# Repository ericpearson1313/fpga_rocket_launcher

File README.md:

### fpga_rocket_launcher

A long-time hobby of mine is model rocketry where I build and fly models rockets in a club setting.
A launch controller has a push button to electrically launch the models safely from a distance.
The controller feeds current from a battery, through a push button and lead wires to a resistive heater to initiate the launch.
For something so simple it causes consternation when the launch countdown reaches zero, button is pressed, and nothing, due to a fault of the controller!
Years of itteratively building launch controllers has not yet acheived personal perfection in launch controller design, but I'm having fun trying.

This repo contains my design files for a digital, capacitive discharch, launch controller. It was designed as a one-off fully instrumented 
launch controller based on a FPGA which enables built in oscilloscope-like capture and HDMI display. This provides aid in bring-up, observation of algorithm improvements and field analysis during fail-to-launch scenarios to understand how a launch fails (and adjust the design algorithms accordingly, and repeat). 

### Updates / Branches

Well this project has evolved alot. 

The launch controller, fully instrumented, gave me alot of observations of sucessful and failed operations. Burn-through makes this a unique control problem, and when obsereved closely is quite chaotic. Through itterative development and testing I updated the control algorithms and circuits. Alot more testing is needed, but the fpga core 'seems' solid, and my understanding of the initiation process has expanded greatly (and I can see alot more to understand).

Given the core fpga algorithms now for a simple handheld launch controller with rock solid operation.  

Integrating a chip deep within a simple device needs the insight of the development logic (ie hdmi) required tooling(fpgas) to breakout, connect, emulate, monitor, and simulating the system, and test the devices. This required a base architecture and plan to take advantage of the simple interconnect (a dozen I/O signals) available using the algorithm. Since this might be some effort,
planning went into the I/O so that it could address a number of device types in case I wanted to re-use it. The handheld controller was designed and is being trialled.

About this time the TinyTapeout.com course occured. This was an opportunity to move the core logic from Fpga to Asic. The same tooling could be used with an Asic too. 

An ASIC was deveoped integrating the launch control chip core. The system model was used as part of the verification test bench. With some time to spare a BIST (built in self test) was added which contained the system model and runs a 65ms truncated system simulation to self validate the hardware. [3D Chip viewer of the actual chip - way cool!](https://gds-viewer.tinytapeout.com/?model=https://ericpearson1313.github.io/tt_eric_launch/tinytapeout.oas&pdk=sky130A)

A quick outline of the different branches that have evolved. The readme docs on the branches are non existant so far.

- main : the fpga launch controller release (V6 = 7298ded) is in regular use.
- lcc_1K : isolated the MVP core and implemented it on a tiny 1k FPGA
- lcc_emu : is the full lauch controller ported to the lcc development board, and then re factoted to use the lcc_1k core and instrument it.
- lcc_mon : is a stand alone monitor that jsut looks at the signals of the LCC. Used to validate correct in system opeation
- lcc_syssim : is a system simulator (in progress) that connects to an LCC to test it.
- lcc_tt : is Tiny Tapeout chip in 130nm on a 0.2 x 0.16 mm die (1x2), it almost fit on a 1x1 tile, but not quite, so utilization is low.
- lccst_tt : is a Tiny Tapeout chip including a full self test (2x2) is 320x200um. The self test logic (a full system simulation) is almost 3x larger than the core, but gives me self test.

The original devlopement doc, where it all started, continues below

# Digital Model Rocket Launch Controller

A FPGA based model rocket digital launch controller.

No embedded CPU, this is Verilog RTL synthesized digital logic.

Showing a bench test using an Estes igniter. Observed low resistance (~ 1ohm) and takes 4 Joules at 4 amps for about 300msec.

[Schematic](fpga_blaster_schem_v0_8.pdf)

### Digital constant current capacitive discharge launch controller.

## Core function

Powered by 4xAA Lithium batteries capable 1A of current. 
When armed, the controller charges a 200uF capactor bank to 320V with a flyback converter giving 10 Joules of stored energy. 
Upon launch, the capacitor is discharged through a 390uH inductor into the igniter.
The discharge is modulated by a FET with a PWM gate drive.
Discharge is digitally current controlled as a buck converter with a setpoint in the range of 2.0 to 6.0 amps.
The set current is maintained over the full capacitor discharge, or until the ignitor burns through and the circuit opens.

The digital control system uses a differential analog front end, used to isolate and instrument the capacitor and output IVs.
12-bit ADCs sample the four signals (cap/out,I/V) which are simultaneously sampled and digitized at 3 Mhz and fed into the digital system.

The PWM signal is generated by a control loop running at 48 Mhz (16x sample rate). 
The control loop models the inductor current based on the PWM signal, ADC capcitor and output voltages (slowly changing), sample rate coil inductance. 
The PWM is turned on when ADC output current falls below a setpoint.
The PWM is turned off when the output current model rises above a setpoint,  
The model used for turn-off to avoid overshoot due to timing accuracy and sample latency.
A stable current pulse is generated limited only by the dropping capacitor voltage with a ripple limited only by the minimum PWM pulse width.

## Extended Functions

Additional uses for FPGA logic and real time ADC data stream can be implemented. These range from simple to Max Headroom.

### Charged LED Hysteresis.

Using the ADC stream include the capacitor voltage, the charge-LED could be operated to reflect the capacitor voltage charge with some hysteresis.
The logic would turn on the charge-LED when the capacitor voltage sample is received and reached 300V, as we want a full charge for launch, 
but would only turn off the charge-LED when the capacitor voltage falls below 50V (<3% energy) as we'ed like to know when it is safe to handle.

```
// Arm is based on vcap with 300v on thresh and 50v off thresh
logic cap_charged;
always @( posedge clk ) begin
	if( reset ) begin
		cap_charged <= 0;
	end else begin
		cap_charged <= ( strobe_d && vcap > (( 300 * 10000 ) / 2005 ) ) ? 1'b1 :
		               ( strobe_d && vcap < (( 50  * 10000 ) / 2005 ) ) ? 1'b0 : cap_charged;
	end
end
```

### Fire Button Debounce and Feedback.

Some dedicated logic to handle the lauch button input is worth while.

To make low cost push button feel nice required: adding debounce logic, and provide audio feedback of its operation. 
To do this debounce counters are used to measure at least 5ms of time before sensing a 'press',
and then generating a fixed 10msec pulse output for logic triggering, and 10msec C5 beep for feedback. 
100ms of release time was required before dectecting another button press. 

Multiple experments and measurements were done to get a basic good enough 'feeling' for this button. The audio feedback worked pleasantly well.

This button also had a long press detect feature to trigger additional functionality. 
If held for 600msec a 2nd signal output would be asserted while held.

### Pulse Energy Accumulation

Ignition energy is a key parameter of igniters. Mensurements
are usefull to check this value.

The instantaneous power (Watts) of the capacitor and outputs can
each be calculated from the ADC samples as E = I * V.

The energy (Joules) over a time period can be accumulated by the sum
of the power measurement.

Using 44 bit sum of product of the unscaled I and V ADC values during ignition period gives allows a 10 Joule range with uJ resolution.
Using the unscaled ADC data elimiates numerical error accumulation. For display the nearest decimal point position was chosen from the 44 bit number
and fixed point hexadecimal coding used for display. 
```
// Acculuate both Cap and Output power products.
always @(posedge clk) begin
	strobe_d <= ad_strobe;
	// P = I * V
   pout[21:0] <= vout[10:0] * iout[10:0];
   pcap[21:0] <= vcap[10:0] * icap[10:0];
	if( strobe_d ) begin
		acc_flag_d <= acc_flag;
		// raw power loaded at flag rise, acculuated during flag, and held afterwards
		eout[43:0] <= ( acc_flag && !acc_flag_d ) ? { 22'b0, pout[21:0] } : ( acc_flag ) ? ({ 22'b0, pout[21:0] } + eout[43:0]) : eout[43:0];
		ecap[43:0] <= ( acc_flag && !acc_flag_d ) ? { 22'b0, pcap[21:0] } : ( acc_flag ) ? ({ 22'b0, pcap[21:0] } + ecap[43:0]) : ecap[43:0];
	end else begin
		acc_flag_d <= acc_flag_d;
		eout[43:0] <= eout[43:0];
		ecap[43:0] <= ecap[43:0];
	end
end
```

Measuring power of both the output and capactor gives insights into the device efficiency and 
some redundancy for measurement validation.

### Continuity Checking

Checking the continuity of an igniter is a resistance measurement to 
check for cases where the circuit is open or shorted.

After the system is armed and waiting for launch, once per second, a 1usec PWM pulse is generated.
Ohms law, R = E / I, is performed on the ADC samples to derive a resistance.

The resistance is averaged and shown to be repeatable over the range 0.4 to 30.0 ohms.

Thresholds are applied to the resistance to decide when the continuity LED is turned on (1.0 to 16 ohms),
and a beep code is generated (A mute dip switch stops the beep codes after the first)

```
1 beep - OK, 1.0 to 8 Ohms
2 beeps - HI, over 8 ohms, but not open
3 beeps - Open circuit,
4 beeps - SHORT circuit maybe, under 1.0 ohms
```
Note: the energy output for this short pulse is accumulated and displayed by the previous function
and usually under 0.25 mJoules which is not enough for ignition.

### HDMI VGA output

Normally on-board LEDs are usefull during development debug to present state to give some insight into
correct operation. Usually there are never enough LEDs as state can get quite involved. 

The next steps usually involve: oscilloscopes, logic analysers, computers and software, however ...

LEDs can be replaced with pixels on an HDMI display. FPGA logic to generate HDMI outputs at XVGA 800x480x60Hz resolution is accomplished
with a 32Mhz pixel clock, and DDR LVDS outputs clocked at 160Mhz giving 320mbit ea for Red, Green and Blue. Digtal counters are used
to generate the video syncronization and maintain the current X and Y locations on the screen.

Connecting an internal signal to a given pixel can be as simple as the logical AND of test signal and desired pixel location, 
with all pels being ORed together to make the video signal
```
assign pel1 = (xcount == 100) & (ycount == 300) & (test_signal1 == 1);
assign pel2 = (xcount == 100) & (ycount == 310) & (test_signal2 == 1);
assign video = pel1 | pel2
```
With some additional logic a font set can be derived giving live text display of binary or hex measurements and dynamic text overlays like:
```
	string_overlay #(.LEN( 9)) _id4 (.clk(hdmi_clk), .reset(reset), .char_x(char_x), .char_y(char_y),
	.ascii_char(ascii_char), .x('h02),.y('h03), .out(id_str[4]), 
	.str(	( zoom == 0 ) ? " 21us/div" :
			( zoom == 1 ) ? " 43us/div" :
			( zoom == 2 ) ? " 85us/div" :
			( zoom == 3 ) ? "170us/div" :
			( zoom == 4 ) ? "340us/div" :
			( zoom == 5 ) ? "680us/div" :
			( zoom == 6 ) ? "1.4ms/div" :
			( zoom == 7 ) ? "2.7ms/div" :
			( zoom == 8 ) ? "5.5ms/div" :
			( zoom == 9 ) ? " 11ms/div" :
			( zoom == 10) ? " 22ms/div" :
			( zoom == 11) ? " 44ms/div" :
			/*zoom == 12)*/ " 87ms/div" ) );
```
Using this method logic was built to allow the display of live values: igniter resistance (ohms), capacitor and output energy (Joules), average ADC binary values, error statuses for ADC channels and PSRAM. Fixed point hex values are used for sake of logic simplicty. Noting that 5 hex digits ~ 1 million is helpful.

### Scrolling Oscilloscope

The 3Mhz ADC samples can have min and max values calculated over longer intervals (1/60s) can be stored
into a 500 sample buffer and plotted and overlayed onto the display giving insight into the coarse
operation of the capacitor charge and discharge without missing a single transient during PWM operation
and allowing sufficient time to visually observer operation. 

This display scrolling is halted 4 seconds after launch to show complete capacitor discharge.

### 32 MBytes Trace Buffer

A PSRAM, or pseudo SRAM, is alow cost ($10), high density (32 Mbytres), high speed (400MBs) sram-like memory, that can connects using only 11 signals. 
It has built in refresh logic, and uses a SPI8 interface for burst access.
A simple controller with an AXI4 interface was developed to configure and 
access the device with 16 byte burst writes, and both 8-byte or 64-byte burst reads.

These PSRAM are only available in ball grid array (BGA) footprints. This was my first home assembled PCB with a BGA. YouTube helped alot for that.

The ADC sampels are stored to a 32 Mbyte circular trace buffer. With 3 Mhz sampling and 64 bits per sample we get 1.3 seconds of storage, which is 
sufficient to capture the full launch operation. 64 bits allows capturing of the 4x 12-bit adc samples, as well as the sampled model (estimated current)
and sampled PWM, and push-button signals as well as an burn-through detect signal.

The buffer is written continuously and only is stopped after launch finished, captureing the full detail from slightly before the launch button is pressed.

### Trace Buffer Display

The 800 samples of data is read from the trace buffer during video blanking and used to plot the sample data multiple scales and colors.
The starting address and stride allows examing the data from very coarse to finest full 3 Mhz detail. 

After launch the fire button is used to step through zoom ranges to see what occured during launch.

### Blipvert

A blipvert is a very brief television advertisement, lasting one second. The term and concept were used in the 1985 film Max Headroom: 20 Minutes into the Future.

HDMI provides a fast and standards compliant way to upload the 32 Mbyte trace buffer to a computer.
The memory is dumped to the RGB video HDMI output, with each visible display line having an memory address
followed by 1 kbyte of data all encoded into the RGB pixels.

This looks like a burst of messy noise, which matched my memory of the blipvert from the film. 

The bipvert is activated by holding down the fire button for at least 1 second and continously dumps the buffer.

Using an HDMI capture card and capturing a second of the video noise gives the entire memory contents,
which can be recovered with a script from the captured video.

#### Blipvert Update #1

The 1st issue is that HDMI capture devices for RGB are costly ($300-$400), but are available
for $20 if a YUV color space is used. That is because the base USB protocol inlcudes support and drivers
for cameras and the cheap HDMI-USB capturee devices only support YUV2 protocol.

So what I planned and did was to switch over to YUV2 during blipvert operation. 
This meant inserting HDMI InfoFrame packets during video blanking, so each viedo frame could be identified
as either RGB24 or YUV2 coded. This swithcing worked.

This raised the 2nd issue was that my awesome and pricy sunlight viewable LCD display only supported the DVI subset of HDMI,
and the presence of InfoFrame packets caused issues. And the HDMI capture device required that the InfoFrames
must always be transmitted (or never transmitted).

The solution was to take advantage of the 2 HDMI ports and simultaneously transmit DVI for the LCD display and HDMI to external devices,
such as the Cheap USB capture device or an LCD display.

### Text Overlay

In addition to the dynamic logic derived text it is useful to have some fixed text overlay.

ROM equivalents for a 5x7 font table and a 16 color text overlay efficiently utilize the FPGA built in SRAMS. 
Unfortuately with this lowest cost (SC) version of the fpga, ROM initialization of the SRAMs is not available,
and the updated device costs 50% more. So logic was added to read the onboard flash and load it into the rom's (SRAMS). 

This text allowed my to display some basic static information without worrying about incremental gate cost if I modified the text.

### Git Commit ID

It is always helpful to be able to trace a running system back to its git commit. 

Some bash and awk scripting was used extract, format, and insert the 7 hex digit git commmit id into the text overlay 
(lower right corner) before the FPGA was compiled. Very handy

## FPGA Selection

The MAX-10 FPGAs from Intel/ALtera were selected as a) free tools were available and b) low cost devices and c) the instant-on (10mSec) boot time.
The 144 pin quad flat pack was chosen as it is hand solderable and probe-able. Devices from 2K to 25K logic cells are avaialable in pin compatible packages.
The free tools support System Verilog design input, and provide support integrating device specific features including differential and DDR IO and PLLs for clock generation. 

The design choice was the Intel Altera 10M04SCE144C8G, breaking down the part number:

```
10M - this family has free software tools.
04 - This was a $20 low cost device, has 4K Logic Elements (LEs) ).
SC - compact(cheap) device, no analog input, limited flash, no rom
E144 - Hand solderable quad flat pack
C - cheap consumer temps only
8G - cheap, slowest speedgrade
```

This 10M04 device also support pin compatibility over a 2 to 25K LE. 

The 10M04 is also a 'limited' device, in that
it is actually an 8K LE device and limited by software to only allow 4K usage. This allow the vendors to sell
their "Floor sweepings", and provides 1/2 cost devices to us. The neat part is that 100% utilization of the 4K LEs is 
then possible as which LEs are used remains flexible, and the interconnect is sized for higher densities, so it can
be fully packed to 99% utilization.

## Free Development Tools 

FPGA Dev Tools : Intel Altera Quartus Prime Lite v23.1

Schematic/PCB  : KiCad 7.0

## Capacitor discharge Pros and Cons

After this experience is a good time to reflect on the trade offs in
capactor discharge launch controllers vs a standard launch controller based with push button.

```
Pros:
+ Current Pulse delivers same power with any cabling
+ safety, can be part of an intrisically safe system
+ Resistance Measurement with 0.1 ohm precision
+ Energy Measurement with 1 uJ precision 
+ Repeatability with constant current with minimal ripple
+ Failure Analysys Data
+ Portable, with small battery
+ Battery Life is extended 
+ Reliability, Feedback gives confidence  

Cons:
- Button - it still needs a push button, and can be replaced by a push button.
- Expensive
- Estes - does not work well with estes igniters
- Complex system
- High Voltage and Arcing
- Majority of limited capacitor energy can be dissipated in launch leads and connections.
```

### A ForgeFPGA-1K implementation

Update: A ForgeFPGA implementation. 

I came across ForgeFPGAs which are 3x3mmm low power low cost ($0.50) FPGA chips containing a respectable 1120 logic cells. 
The 24 pins package had the IO needed and the logic cells seemed appropriate for a the launch controllers core functions.
The free tools for synthesis and place-route worked with my verilog code with minor tweaking.
With functional simplification (eg: no hdmi video, no dividers) the tools fit the core launch controller logic gates into 
the ForgeFPGA-1K and generated power and timing reports. 
I then verified the forgefpga verilog by embedding it into my altera max10 fpga launch controller allowing me to view the instrumented interface 
 between the co-synthesized core ForgeFPGA and the real hardware (very nice!).
I plan to use this launch control fpga for an minimalist handheld digital launch controller PCB. It would have connectors for mounting the ForgeFPGA Eval board for development, and would otherwise re-use the ADC and power circuitry interface as needed from the previous controller.

With the size of the FPGA now reduced to basically nothing, a compact size could be looked at. I stopped and considered the shapes limited by the large components: 4xAA, 2x Caps, 1x Coil, and along with output jacks. 3D printing each allowed some ergonomic testing and locating the 2 pairs of buttons and Leds.

A starting layout of the PCB using the landscape packing was chosen from among the models.
The landscape form factor nicely extends to put a connector for the ForgeFPGA evaluation board to be plugged into. That part of the PCB is intended to be cut away (but could be integrated into a taller handheld unit). Mouting land for a spare FPGA is nice. The isolation of high voltage areas is considered from the beginning.  The isolation barrier and components crossing it are clear and visible.
The layout packed the high power connections to the top center of the PCB.

Prior to fully detailing the PCB outline and button/led positions and clearnaces are needed.
I wanted to integrate the leds and buttons into the enclosure. Light pipes for the leds, and frogs
for the buttons. (frog aka pushbutton-with-integrated-spring-for-tactile-switch).
A basic 3d printed model of the enclosure was printed to see how it feels and test the frogs.
I definitely want it thinner and rounded/bevelled. The influence of this model will be far reaching in
the final design. 

Next steps for the minimalist fpga launch controller will be parts ordering, pcb tapeout, and initial 3d enclosure and development stands ...

Its a good point to pause and consider things. So I'm going to loop back and re-examine everything before committing to the next design...

# A Chip ...

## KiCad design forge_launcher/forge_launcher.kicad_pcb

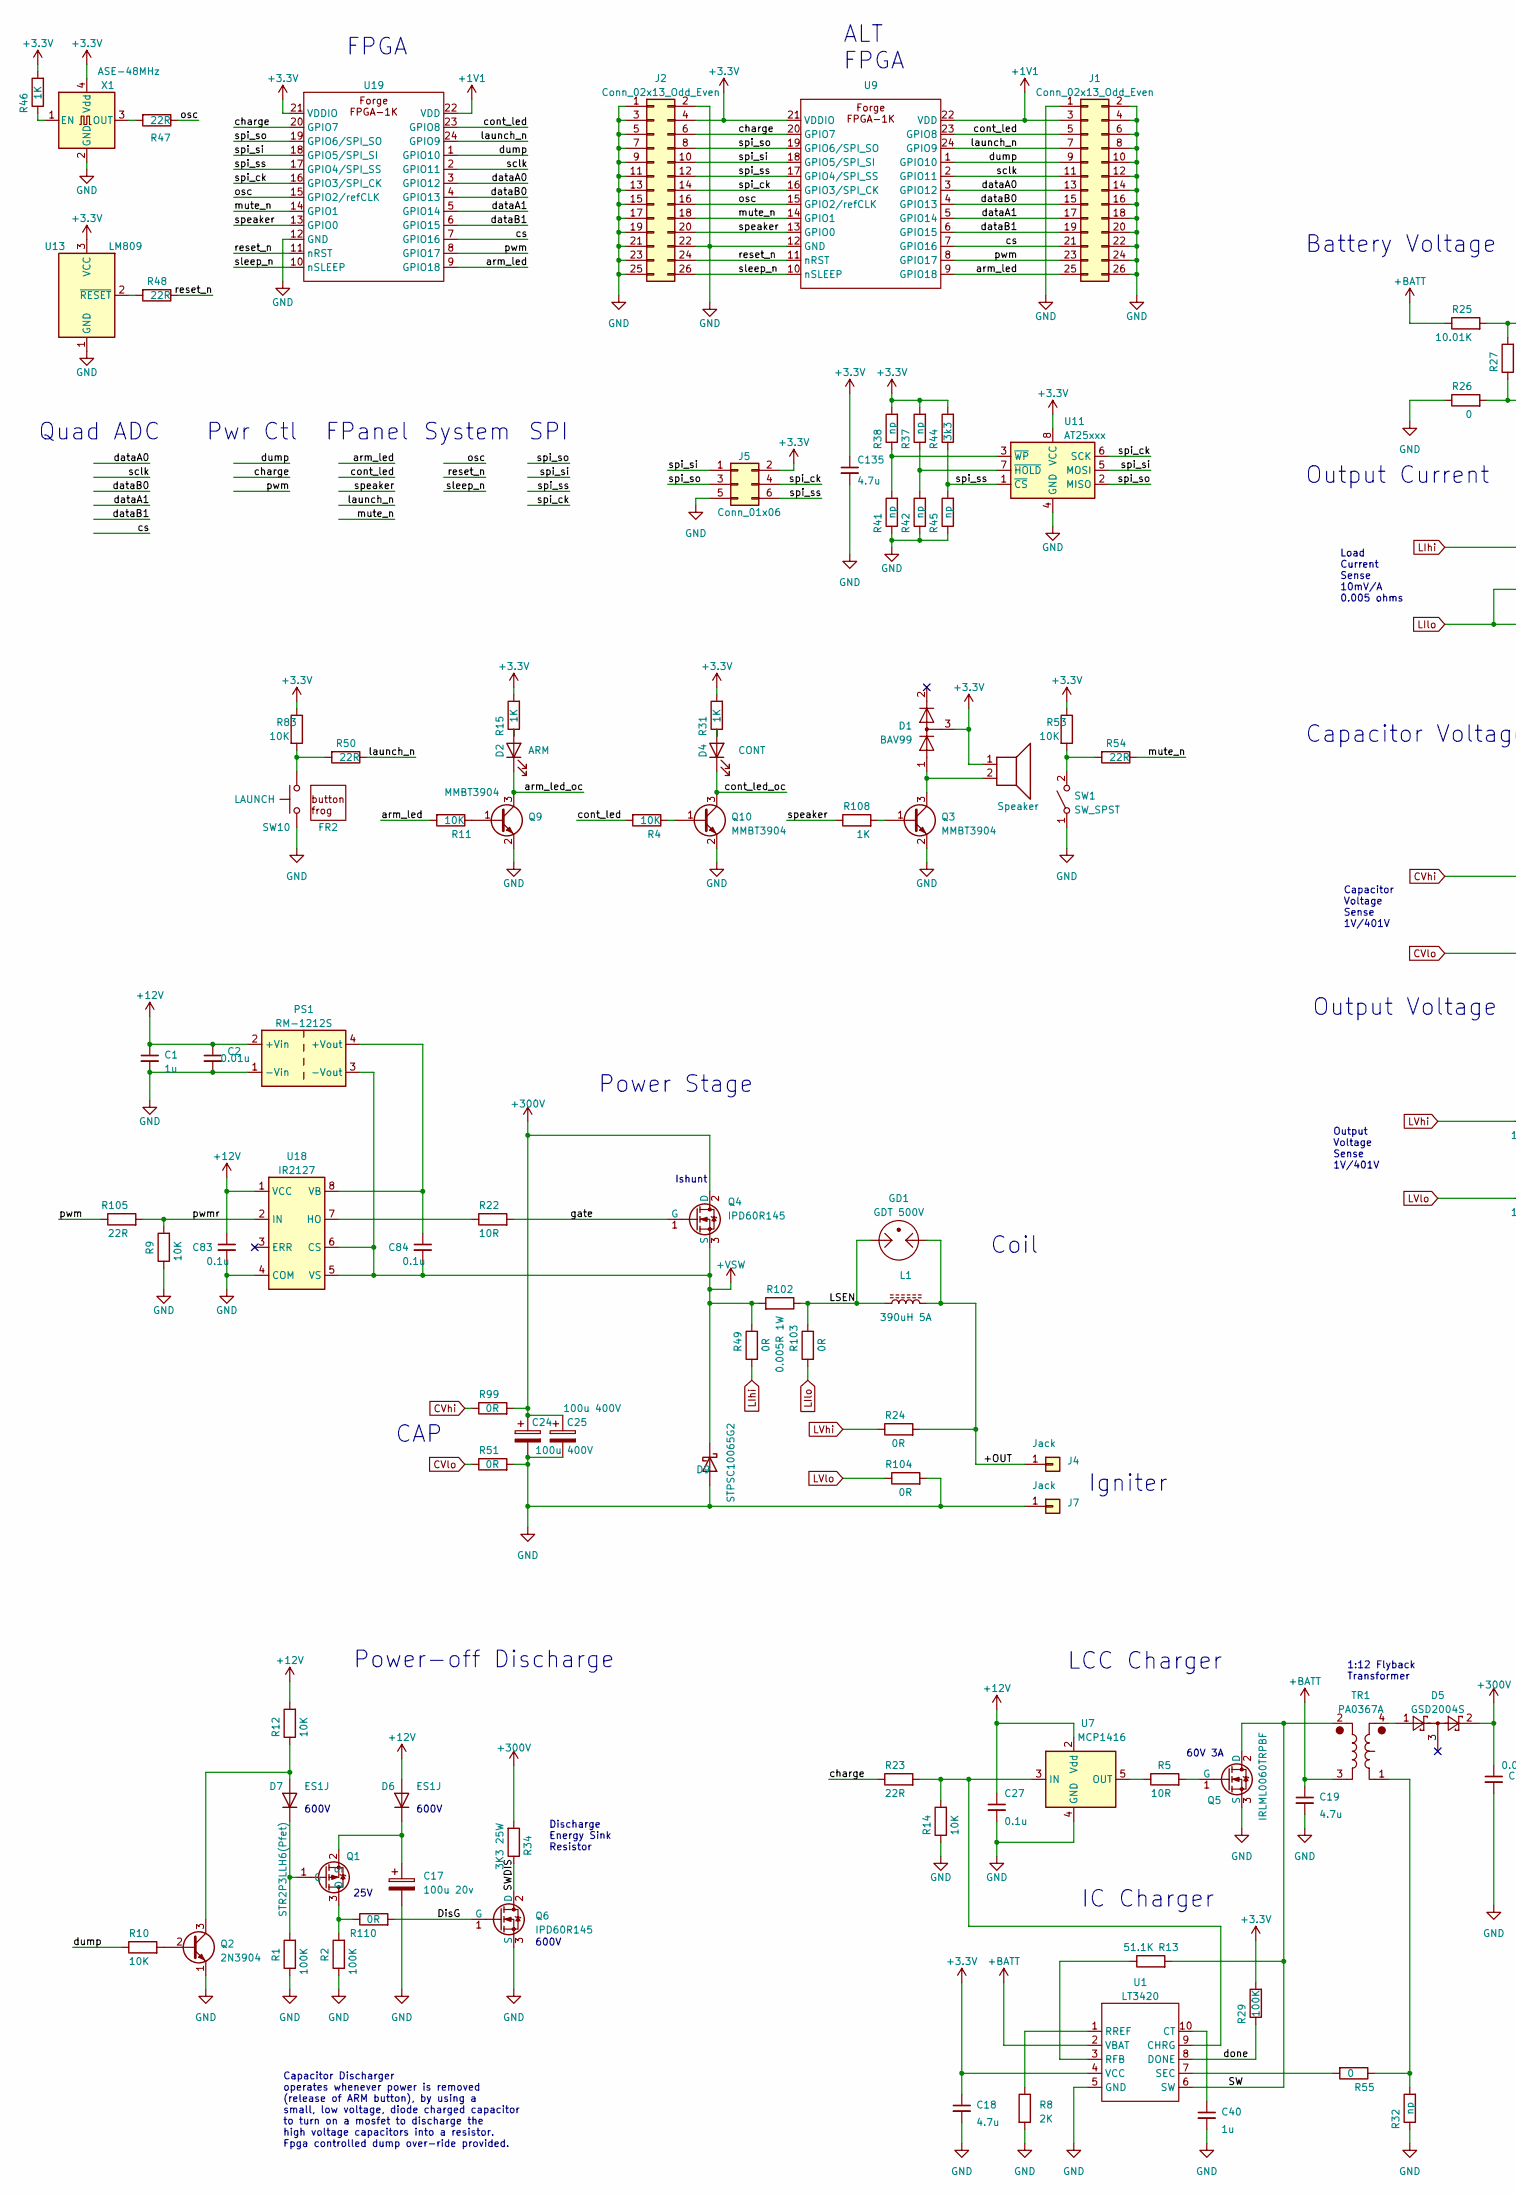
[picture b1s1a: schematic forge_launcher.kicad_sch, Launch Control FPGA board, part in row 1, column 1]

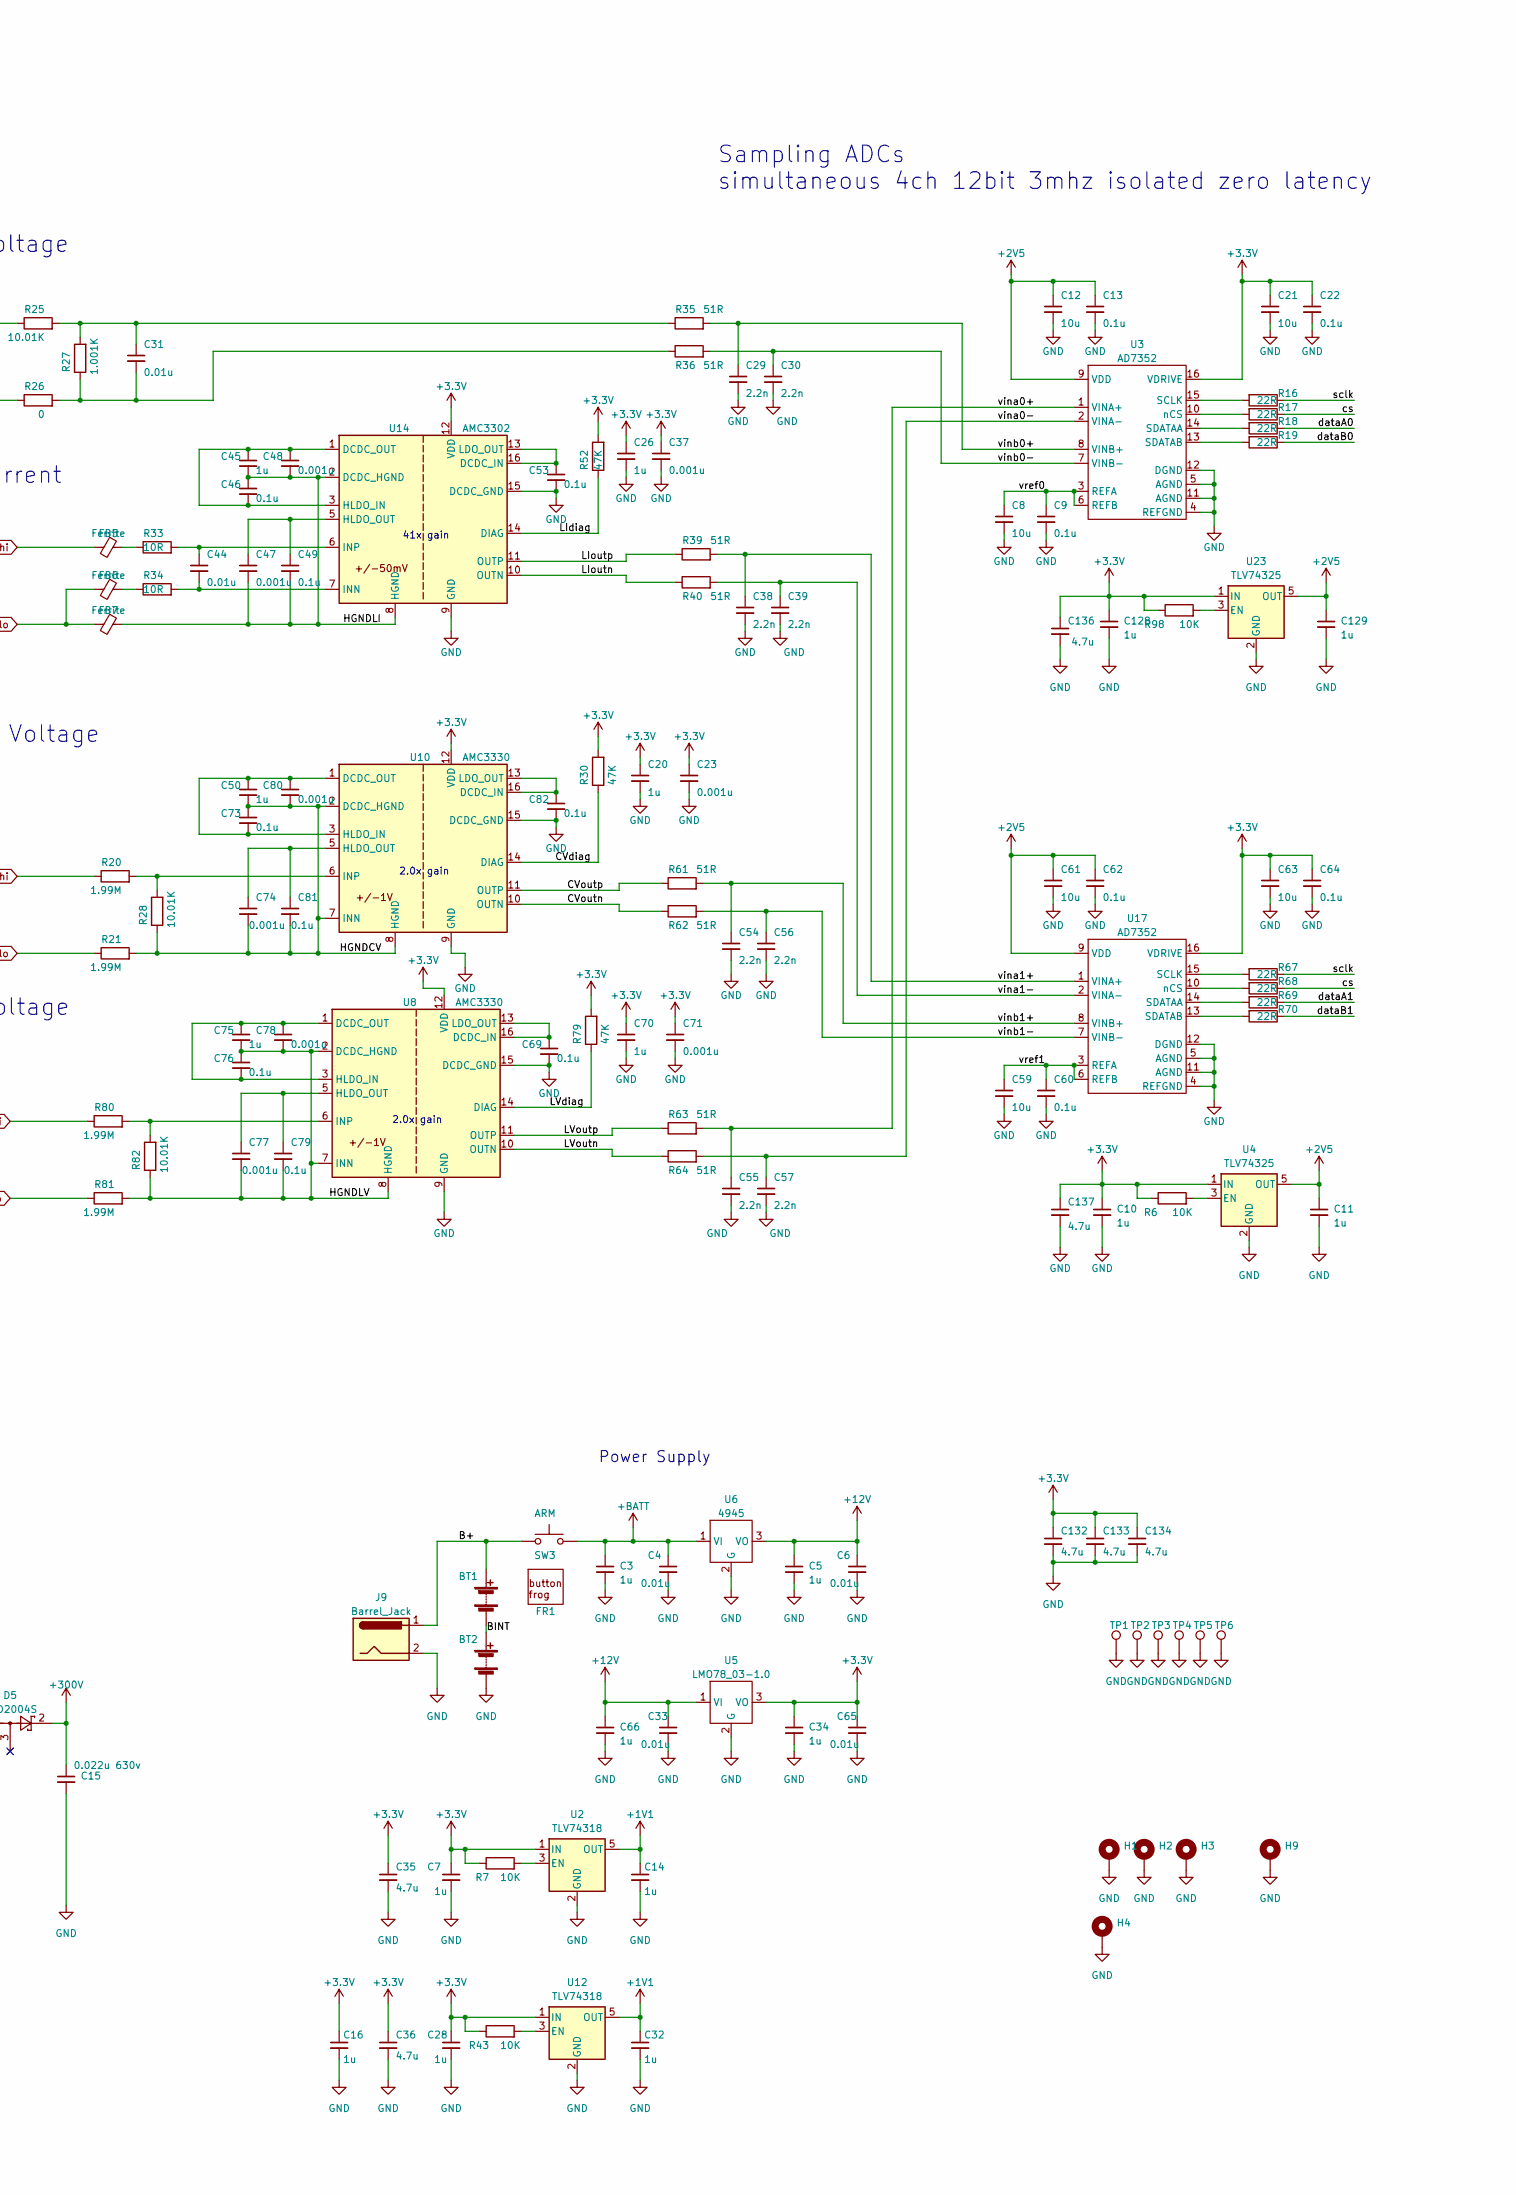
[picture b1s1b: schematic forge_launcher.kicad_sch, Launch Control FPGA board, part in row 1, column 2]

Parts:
BT1, BT2: BatteryHolder_Keystone_2462_2xAA
C1, C3, C5, C7, C10, C11, C14, C16, C20, C26, C28, C32, C34, C40, C45, C50, C66, C70, C75, C128, C129: 1u; C_0603_1608Metric
C2, C4, C6, C31, C33, C44, C65: 0.01u; C_0603_1608Metric
C8, C12, C21, C59, C61, C63: 10u; C_1206_3216Metric
C9, C13, C22, C27, C46, C49, C53, C60, C62, C64, C69, C73, C76, C79, C81, C82, C83, C84: 0.1u; C_0603_1608Metric
C15: 0.022u 630v; C_1206_3216Metric
C17: 100u 20v; C_Radial_D5.0mm_H7.0mm_P2.00mm
C18, C19, C35, C36, C132, C133, C134, C135, C136, C137: 4.7u; C_1206_3216Metric
C23, C37, C47, C48, C71, C74, C77, C78, C80: 0.001u; C_0603_1608Metric
C24, C25: 100u 400V; CP_Radial_D16.0mm_P7.50mm
C29, C30, C38, C39, C54, C55, C56, C57: 2.2n; C_0603_1608Metric
D1: BAV99; SOT-23
D2: ARM; LED_0603_1608Metric
D4: CONT; LED_0603_1608Metric
D5: GSD2004S; SOT-23; JLC C85606
D6, D7: ES1J; D_SMA; JLC C99410
D9: ‎STPSC10065G2; TO-263-2_TabPin1; JLC C602663
FB5, FB6, FB7: Ferrite; L_0603_1608Metric
FR1, FR2: button_frog
GD1: GDT 500V; C_1812_4532Metric_Pad1.57x3.40mm_HandSolder
H1, H2, H3, H4, H9: MountingHole_3mm_Pad
J1, J2: Conn_02x13_Odd_Even
J4, J7: Jack; CalTest_CT3151
J5: Conn_01x06; PinHeader_2x03_P2.54mm_Vertical
J9: Barrel_Jack; BarrelJack_CUI_PJ-063AH_Horizontal
L1: 390uH 5A; L_Toroid_Vertical_L35.6mm_W17.8mm_P12.70mm_Pulse_E
LS1: Speaker; PUIAudio_SMT_0825_S_4_R
PS1: RM-1212S; Converter_DCDC_Murata_MEE1SxxxxSC_THT
Q1: STR2P3LLH6(Pfet); SOT-23
Q2: 2N3904; SOT-23
Q3, Q9, Q10: MMBT3904; SOT-23
Q4, Q6: IPD60R145; TO-252-2; JLC C3277918
Q5: IRLML0060TRPBF; SOT-23; JLC C3277918
R1, R2, R29: 100K; R_0603_1608Metric; JLC C319967
R4, R11: 10K; R_0603_1608Metric; JLC C319967
R5, R22, R33, R34: 10R; R_0603_1608Metric; JLC C778416
R6, R7, R43, R98: 10K; R_0603_1608Metric; JLC C778416
R8: 2K; R_0603_1608Metric; JLC C319700
R9, R12, R14, R53, R83: 10K; R_0603_1608Metric; JLC C491211
R10: 10K; R_0603_1608Metric
R13: 51.1K; R_0603_1608Metric; JLC C234563
R15, R31, R46, R108: 1K; R_0603_1608Metric; JLC C319967
R16, R17, R18, R19, R47, R48, R50, R54, R67, R68, R69, R70: 22R; R_0603_1608Metric; JLC C319967
R20, R21, R80, R81: 1.99M; R_0603_1608Metric; JLC C778416
R23, R105: 22R; R_0603_1608Metric; JLC C778416
R24, R49, R51, R99, R103, R104: 0R; R_0603_1608Metric; JLC C778416
R25, R28, R82: 10.01K; R_0603_1608Metric; JLC C778416
R26: 0; R_0603_1608Metric; JLC C778416
R27: 1.001K; R_0603_1608Metric; JLC C778416
R30, R52, R79: 47K; R_0603_1608Metric; JLC C778416
R32, R37, R38, R41, R42, R45: np; R_0603_1608Metric; JLC C319967
R35, R36, R39, R40, R61, R62, R63, R64: 51R; R_0603_1608Metric; JLC C778416
R44: 3k3; R_0603_1608Metric; JLC C319967
R55: 0; R_0603_1608Metric; JLC C319967
R102: 0.005R 1W; R_2818 current sense
R110: 0R; R_0603_1608Metric; JLC C319967
SW1: SW_SPST; SW_E-Switch_EG1224_SPDT_Angled
SW3: ARM; SW_SPST_HP03
SW10: LAUNCH; SW_SPST_HP03
TP1, TP2, TP3, TP4, TP5, TP6: TestPoint_Keystone_5000-5004_Miniature
TR1: PA0367A; PA0637A Pulse Coil 3D; JLC C5382098
U1: LT3420; MSOP-10_3x3mm_P0.5mm; JLC C670531
U2, U12: TLV74318; SOT-23-5
U3, U17: AD7352; TSSOP-16_4.4x5mm_P0.65mm
U4, U23: TLV74325; SOT-23-5
U5: LMO78_03-1.0; Converter_DCDC_Murata_OKI-78SR_Horizontal
U6: 4945; Converter_DCDC_Murata_OKI-78SR_Horizontal
U7: MCP1416; SOT-23-5
U8, U10: AMC3330; SOIC-16W_7.5x10.3mm_P1.27mm
U9, U19: QFN-24-3x3mm
U11: AT25xxx; SOIC-8_3.9x4.9mm_P1.27mm
U13: LM809; SOT-23
U14: AMC3302; SOIC-16W_7.5x10.3mm_P1.27mm
U18: IR2127; SOIC-8_3.9x4.9mm_P1.27mm; JLC C356723
X1: ASE-48MHz; Oscillator_SMD_Abracon_ASV-4Pin_7.0x5.1mm_HandSoldering

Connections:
+1V1: C14.1, C32.1, J1.3, U2.5 (OUT), U9.22 (VDD), U12.5 (OUT), U19.22 (VDD)
+2V5: C11.1, C12.1, C13.1, C61.1, C62.1, C129.1, U3.9 (VDD), U4.5 (OUT), U17.9 (VDD), U23.5 (OUT)
+3.3V: C7.1, C10.1, C16.1, C18.1, C20.1, C21.1, C22.1, C23.1, C26.1, C28.1, C34.1, C35.1, C36.1, C37.1, C63.1, C64.1, C65.1, C70.1, C71.1, C128.1, C132.1, C133.1, C134.1, C135.1, C136.1, C137.1, D1.3 (K), J2.4, J5.2, LS1.1, R6.1, R7.1, R15.2, R29.2, R30.2, R31.2, R37.2, R38.2, R43.1, R44.2, R46.2, R52.2, R53.1, R79.2, R83.1, R98.1, U1.4 (VCC), U2.1 (IN), U3.16 (VDRIVE), U4.1 (IN), U5.3 (VO), U8.12 (VDD), U9.21 (VDDIO), U10.12 (VDD), U11.8 (VCC), U12.1 (IN), U13.3 (VCC), U14.12 (VDD), U17.16 (VDRIVE), U19.21 (VDDIO), U23.1 (IN), X1.4 (Vdd)
+12V: C1.1, C2.1, C5.1, C6.1, C27.1, C33.1, C66.1, C83.1, D6.2 (A), PS1.2 (+Vin), R12.2, U5.1 (VI), U6.3 (VO), U7.2 (Vdd), U18.1 (VCC)
+BATT: C3.1, C4.1, C19.1, R25.1, SW3.2, TR1.3, U1.2 (VBAT), U6.1 (VI)
+VSW: C84.2, D9.1 (K), PS1.3 (-Vout), Q4.3 (S), R49.1, R102.2, U18.5 (VS), U18.6 (CS)
/+OUT: GD1.1, J4.1, L1.2, R24.2
/B+: BT1.1 (+), J9.1, SW3.1
/BINT: BT1.2 (-), BT2.1 (+)
/CVdiag: R30.1, U10.14 (DIAG)
/CVoutn: R62.1, U10.10 (OUTN)
/CVoutp: R61.1, U10.11 (OUTP)
/DisG: Q6.1 (G), R110.2
/HGNDCV: C50.2, C73.1, C74.2, C80.2, C81.2, R21.2, R28.1, U10.2 (DCDC_HGND), U10.7 (INN), U10.8 (HGND)
/HGNDLI: C45.2, C46.1, C47.2, C48.2, C49.2, FB7.1, U14.2 (DCDC_HGND), U14.8 (HGND)
/HGNDLV: C75.2, C76.1, C77.2, C78.2, C79.2, R81.2, R82.1, U8.2 (DCDC_HGND), U8.7 (INN), U8.8 (HGND)
/LIdiag: R52.1, U14.14 (DIAG)
/LIoutn: R40.1, U14.10 (OUTN)
/LIoutp: R39.1, U14.11 (OUTP)
/LSEN: GD1.3, L1.1, R102.1, R103.1
/LVdiag: R79.1, U8.14 (DIAG)
/LVoutn: R64.1, U8.10 (OUTN)
/LVoutp: R63.1, U8.11 (OUTP)
/SW: Q5.2 (D), R13.2, TR1.2, U1.6 (SW)
/arm_led: J1.25, R11.2, U9.9 (GPIO18), U19.9 (GPIO18)
/arm_led_oc: D2.1 (K), Q9.3 (C)
/charge: J2.6, R23.1, U9.20 (GPIO7), U19.20 (GPIO7)
/cont_led: J1.5, R4.2, U9.23 (GPIO8), U19.23 (GPIO8)
/cont_led_oc: D4.1 (K), Q10.3 (C)
/cs: J1.21, R17.1, R68.1, U9.7 (GPIO16), U19.7 (GPIO16)
/dataA0: J1.13, R18.1, U9.3 (GPIO12), U19.3 (GPIO12)
/dataA1: J1.17, R69.1, U9.5 (GPIO14), U19.5 (GPIO14)
/dataB0: J1.15, R19.1, U9.4 (GPIO13), U19.4 (GPIO13)
/dataB1: J1.19, R70.1, U9.6 (GPIO15), U19.6 (GPIO15)
/done: R29.1, U1.8 (DONE)
/dump: J1.9, R10.1, U9.1 (GPIO10), U19.1 (GPIO10)
/gate: Q4.1 (G), R22.2
/launch_n: J1.7, R50.1, U9.24 (GPIO9), U19.24 (GPIO9)
/mute_n: J2.18, R54.1, U9.14 (GPIO1), U19.14 (GPIO1)
/osc: J2.16, R47.1, U9.15 (GPIO2/refCLK), U19.15 (GPIO2/refCLK)
/pwm: J1.23, R105.1, U9.8 (GPIO17), U19.8 (GPIO17)
/pwmr: R9.2, R105.2, U18.2 (IN)
/reset_n: J2.24, R48.1, U9.11 (nRST), U19.11 (nRST)
/sclk: J1.11, R16.1, R67.1, U9.2 (GPIO11), U19.2 (GPIO11)
/sleep_n: J2.26, U9.10 (nSLEEP), U19.10 (nSLEEP)
/speaker: J2.20, R108.1, U9.13 (GPIO0), U19.13 (GPIO0)
/spi_ck: J2.14, J5.4, U9.16 (GPIO3/SPI_CK), U11.6 (SCK), U19.16 (GPIO3/SPI_CK)
/spi_si: J2.10, J5.1, U9.18 (GPIO5/SPI_SI), U11.5 (MOSI), U19.18 (GPIO5/SPI_SI)
/spi_so: J2.8, J5.3, U9.19 (GPIO6/SPI_SO), U11.2 (MISO), U19.19 (GPIO6/SPI_SO)
/spi_ss: J2.12, J5.6, R44.1, R45.2, U9.17 (GPIO4/SPI_SS), U11.1 (~CS), U19.17 (GPIO4/SPI_SS)
/vina0+: C55.1, R63.2, U3.1 (VINA+)
/vina0-: C57.1, R64.2, U3.2 (VINA-)
/vina1+: C38.1, R39.2, U17.1 (VINA+)
/vina1-: C39.1, R40.2, U17.2 (VINA-)
/vinb0+: C29.1, R35.2, U3.8 (VINB+)
/vinb0-: C30.1, R36.2, U3.7 (VINB-)
/vinb1+: C54.1, R61.2, U17.8 (VINB+)
/vinb1-: C56.1, R62.2, U17.7 (VINB-)
/vref0: C8.1, C9.1, U3.3 (REFA), U3.6 (REFB)
/vref1: C59.1, C60.1, U17.3 (REFA), U17.6 (REFB)
CVhi: R20.1, R99.1
CVlo: R21.1, R51.1
GND: BT2.2 (-), C1.2, C2.2, C3.2, C4.2, C5.2, C6.2, C7.2, C8.2, C9.2, C10.2, C11.2, C12.2, C13.2, C14.2, C15.2, C16.2, C17.2, C18.2, C19.2, C20.2, C21.2, C22.2, C23.2, C24.2, C25.2, C26.2, C27.2, C28.2, C29.2, C30.2, C32.2, C33.2, C34.2, C35.2, C36.2, C37.2, C38.2, C39.2, C40.2, C53.2, C54.2, C55.2, C56.2, C57.2, C59.2, C60.2, C61.2, C62.2, C63.2, C64.2, C65.2, C66.2, C69.2, C70.2, C71.2, C82.2, C83.2, C128.2, C129.2, C132.2, C133.2, C134.2, C135.2, C136.2, C137.2, D9.2 (A), H1.1, H2.1, H3.1, H4.1, H9.1, J1.1, J1.2, J1.4, J1.6, J1.8, J1.10, J1.12, J1.14, J1.16, J1.18, J1.20, J1.22, J1.24, J1.26, J2.1, J2.2, J2.3, J2.5, J2.7, J2.9, J2.11, J2.13, J2.15, J2.17, J2.19, J2.21, J2.22, J2.23, J2.25, J5.5, J7.1, J9.2, PS1.1 (-Vin), Q2.1 (E), Q3.2 (E), Q5.3 (S), Q6.3 (S), Q9.2 (E), Q10.2 (E), R1.1, R2.1, R8.2, R9.1, R14.1, R26.1, R32.1, R41.1, R42.1, R45.1, R51.2, R104.2, SW1.1 (A), SW10.1, TP1.1, TP2.1, TP3.1, TP4.1, TP5.1, TP6.1, U1.5 (GND), U2.2 (GND), U3.4 (REFGND), U3.5 (AGND), U3.11 (AGND), U3.12 (DGND), U4.2 (GND), U5.2 (G), U6.2 (G), U7.4 (GND), U8.9 (GND), U8.15 (DCDC_GND), U9.12 (GND), U10.9 (GND), U10.15 (DCDC_GND), U11.4 (GND), U12.2 (GND), U13.1 (GND), U14.9 (GND), U14.15 (DCDC_GND), U17.4 (REFGND), U17.5 (AGND), U17.11 (AGND), U17.12 (DGND), U18.4 (COM), U19.12 (GND), U23.2 (GND), X1.2 (GND)
LIhi: FB5.2, R49.2
LIlo: FB6.2, FB7.2, R103.2
LVhi: R24.1, R80.1
LVlo: R81.1, R104.1
unnamed: C31.1, R25.2, R27.2, R35.1
unnamed: C31.2, R26.2, R27.1, R36.1
unnamed: D2.2 (A), R15.1
unnamed: D4.2 (A), R31.1
unnamed: D5.1, TR1.4
unnamed: C17.1, D6.1 (K), Q1.2 (S)
unnamed: D7.2 (A), Q2.3 (C), R12.1
unnamed: D7.1 (K), Q1.1 (G), R1.2
unnamed: FB5.1, R33.1
unnamed: C84.1, PS1.4 (+Vout), U18.8 (VB)
unnamed: Q1.3 (D), R2.2, R110.1
unnamed: Q2.2 (B), R10.2
unnamed: Q3.1 (B), R108.2
unnamed: D1.1 (K), LS1.2, Q3.3 (C)
unnamed: Q5.1 (G), R5.2
unnamed: Q9.1 (B), R11.1
unnamed: Q10.1 (B), R4.1
unnamed: R32.2, R55.1, TR1.1
unnamed: R50.2, R83.2, SW10.2
unnamed: R53.2, R54.2, SW1.2 (B)
unnamed: R14.2, R23.2, U1.9 (CHRG), U7.3 (IN)
unnamed: C40.1, U1.10 (CT)
unnamed: R13.1, U1.3 (RFB)
unnamed: R8.1, U1.1 (RREF)
unnamed: R55.2, U1.7 (SEC)
unnamed: R7.2, U2.3 (EN)
unnamed: R16.2, U3.15 (SCLK)
unnamed: R18.2, U3.14 (SDATAA)
unnamed: R19.2, U3.13 (SDATAB)
unnamed: R17.2, U3.10 (nCS)
unnamed: R6.2, U4.3 (EN)
unnamed: R5.1, U7.5 (OUT)
unnamed: C69.1, U8.13 (LDO_OUT), U8.16 (DCDC_IN)
unnamed: C75.1, C76.2, C78.1, U8.1 (DCDC_OUT), U8.3 (HLDO_IN)
unnamed: C77.1, C79.1, U8.5 (HLDO_OUT)
unnamed: R80.2, R82.2, U8.6 (INP)
unnamed: C82.1, U10.13 (LDO_OUT), U10.16 (DCDC_IN)
unnamed: C50.1, C73.2, C80.1, U10.1 (DCDC_OUT), U10.3 (HLDO_IN)
unnamed: C74.1, C81.1, U10.5 (HLDO_OUT)
unnamed: R20.2, R28.2, U10.6 (INP)
unnamed: R37.1, R42.2, U11.7 (~HOLD)
unnamed: R38.1, R41.2, U11.3 (~WP)
unnamed: R43.2, U12.3 (EN)
unnamed: R48.2, U13.2 (~RESET)
unnamed: C53.1, U14.13 (LDO_OUT), U14.16 (DCDC_IN)
unnamed: C45.1, C46.2, C48.1, U14.1 (DCDC_OUT), U14.3 (HLDO_IN)
unnamed: C47.1, C49.1, U14.5 (HLDO_OUT)
unnamed: C44.1, R33.2, U14.6 (INP)
unnamed: R67.2, U17.15 (SCLK)
unnamed: R69.2, U17.14 (SDATAA)
unnamed: R70.2, U17.13 (SDATAB)
unnamed: R68.2, U17.10 (nCS)
unnamed: R22.1, U18.7 (HO)
unnamed: R98.2, U23.3 (EN)
unnamed: R46.1, X1.1 (EN)
unnamed: R47.2, X1.3 (OUT)

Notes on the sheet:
600V
Power-off Discharge
Igniter
Quad ADC
Capacitor Voltage
41x gain
Coil
Capacitor Voltage Sense 1V/401V
Output Voltage
SPI
Ishunt
Output Voltage Sense 1V/401V
Sampling ADCs simultaneous 4ch 12bit 3mhz isolated zero latency
CAP
2.0x gain
FPGA
25V
IC Charger
System
Pwr Ctl
FPanel
ALT FPGA
Discharge Energy Sink Resistor
60V 3A
Power Supply
Power Stage
Output Current
Battery Voltage
Load Current Sense 10mV/A 0.005 ohms
Capacitor Discharger operates whenever power is removed (release of ARM button), by using a small, low voltage, diode charged capacitor to turn on a mosfet to discharge the high voltage capacitors into a resistor. Fpga controlled dump over-ride provided.
1:12 Flyback Transformer
LCC Charger

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
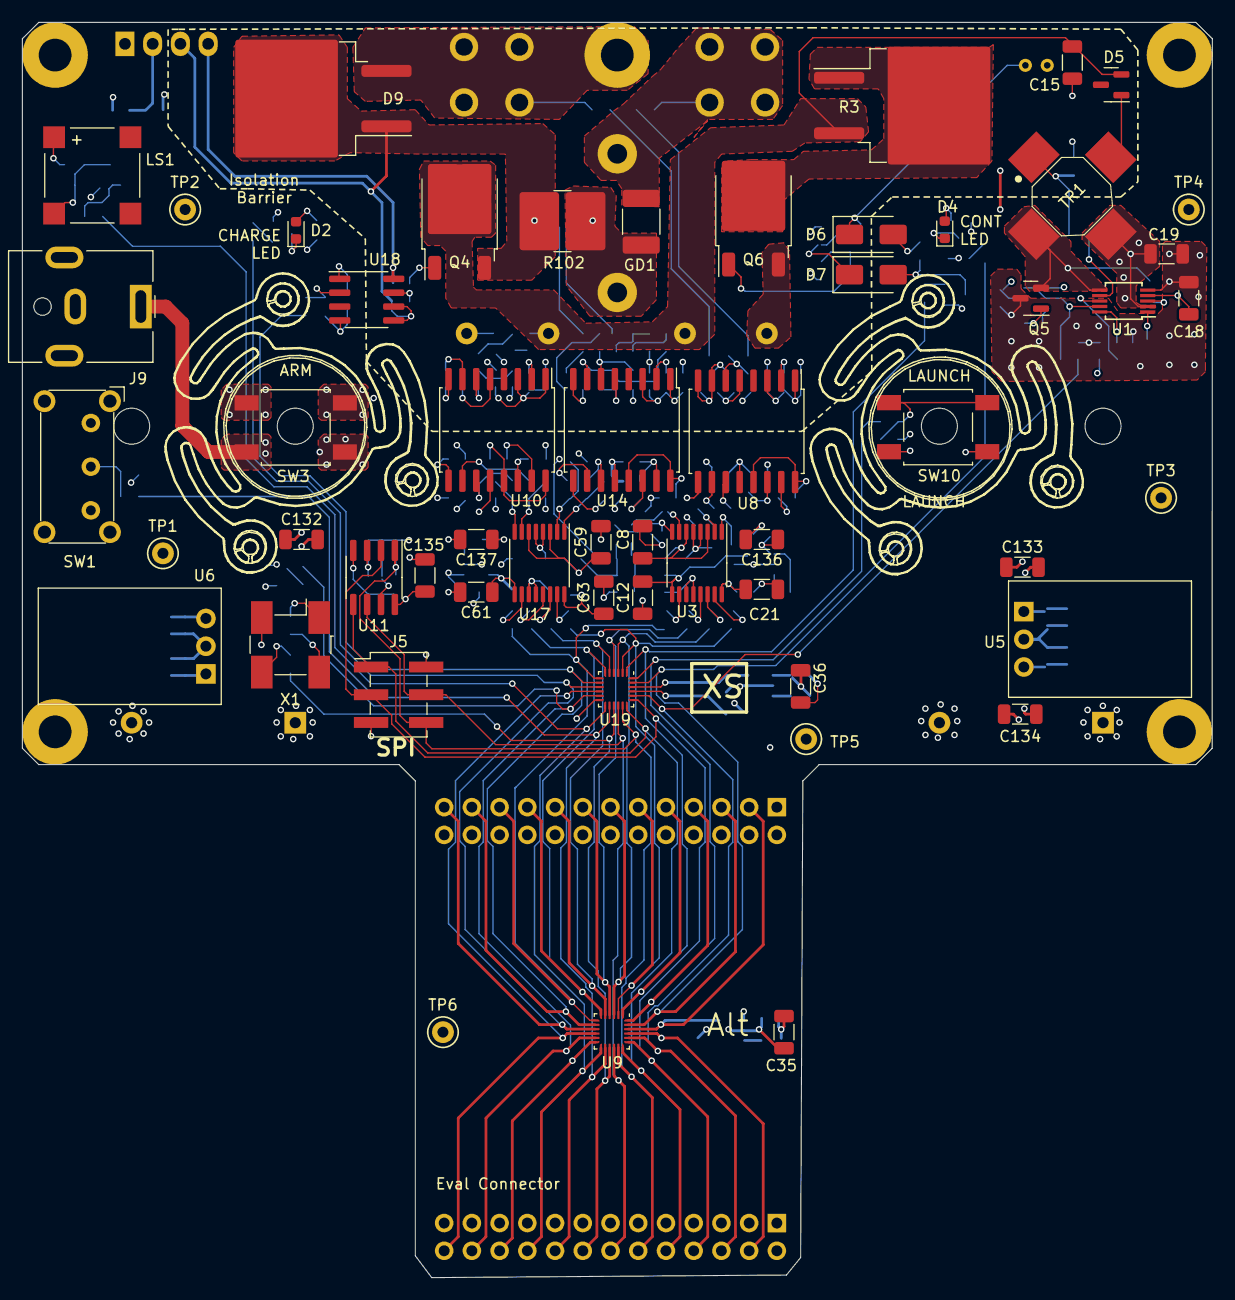
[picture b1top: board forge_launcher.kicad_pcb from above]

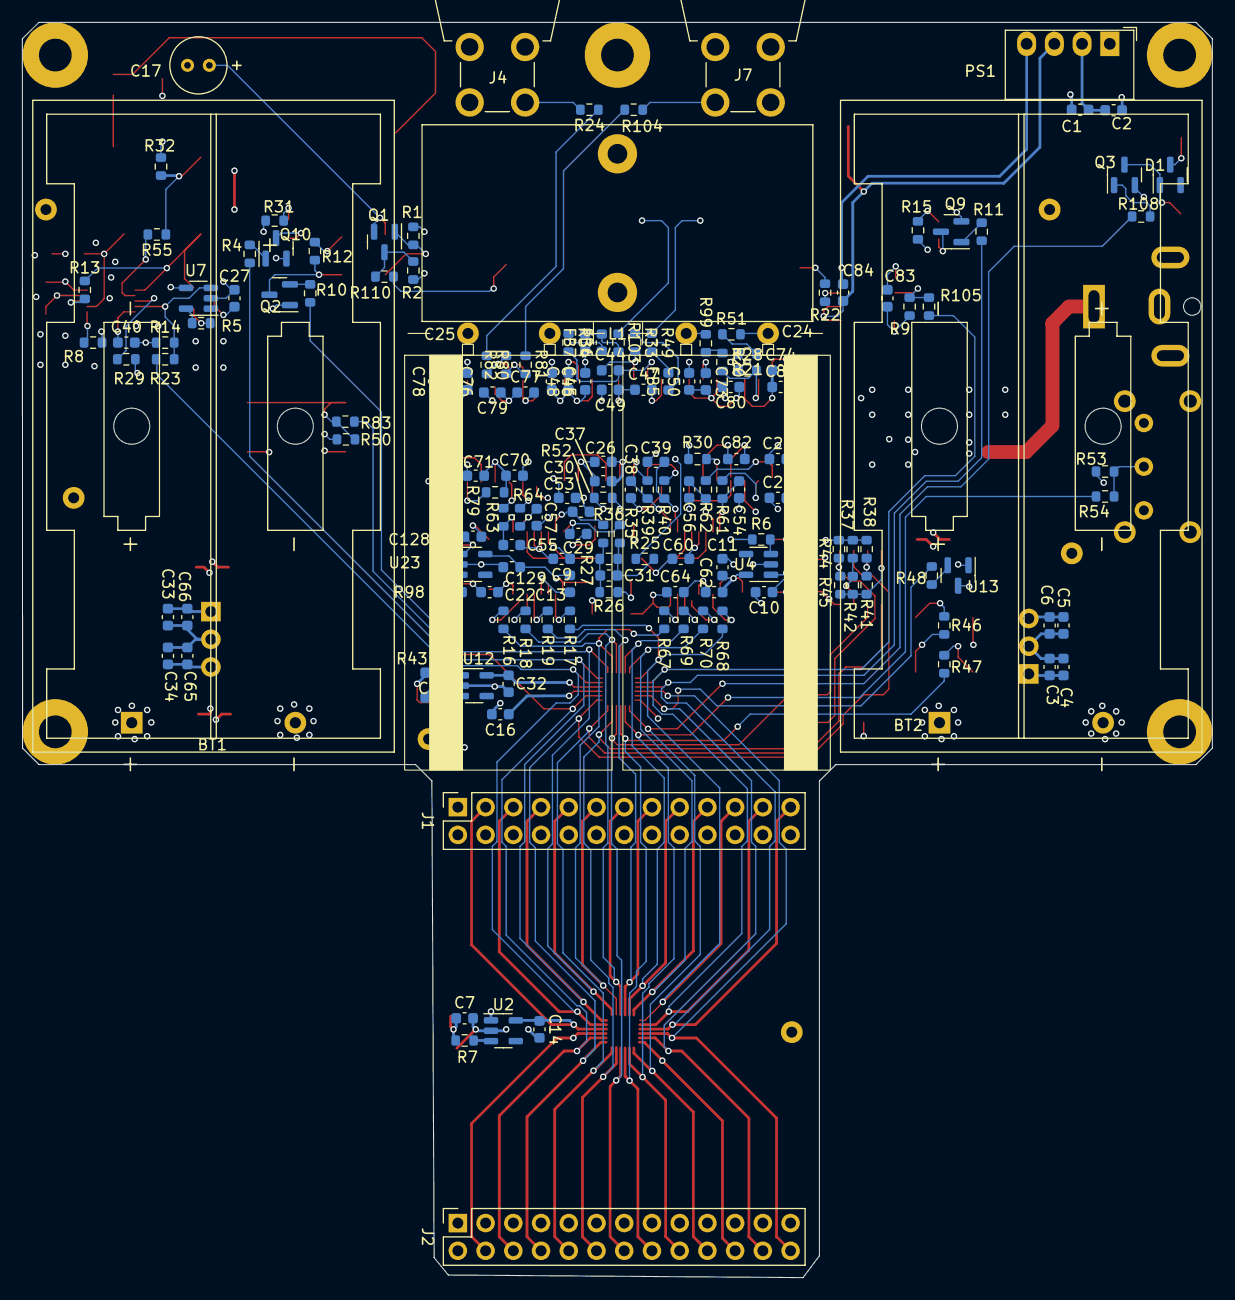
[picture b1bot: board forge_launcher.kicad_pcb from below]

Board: 6 copper layers, 109.0 x 115.0 mm, 225 parts (163 on the bottom side), 127 nets.

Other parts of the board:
R3: 3K3 25W; TO-263-2_TabPin1

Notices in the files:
blaster.qsf:
Copyright (C) 2023  Intel Corporation. All rights reserved.
